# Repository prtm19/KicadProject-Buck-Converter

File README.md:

Hello, this is my project, Buck Converter. We convert 12V DC to 5V DC using a voltage Regulator. In our project, we use LM2496 Voltage regulator IC.

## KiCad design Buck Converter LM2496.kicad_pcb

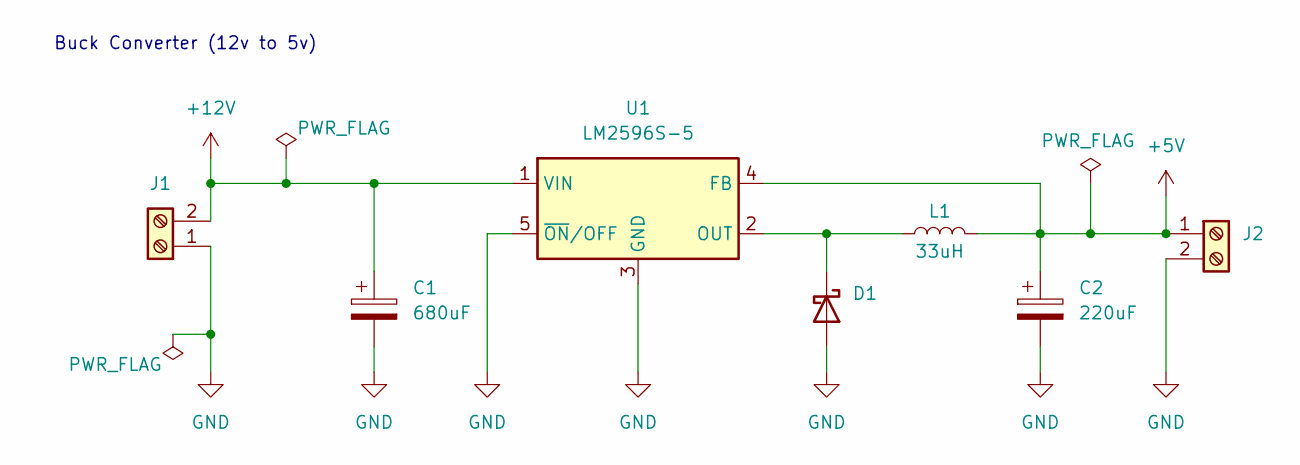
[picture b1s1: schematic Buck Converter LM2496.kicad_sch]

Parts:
C1: 680uF; CP_Radial_D8.0mm_P5.00mm
C2: 220uF; CP_Radial_D6.3mm_P2.50mm
D1: D_Schottky; D_SMA
J1, J2: Screw_Terminal_01x02; TerminalBlock_Phoenix_MKDS-1,5-2-5.08_1x02_P5.08mm_Horizont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
L1: 33uH; L_APV_APH0840
U1: LM2596S-5; TO-263-5_TabPin3

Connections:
+5V: C2.1, J2.1, L1.2, U1.4 (FB)
+12V: C1.1, J1.2, U1.1 (VIN)
GND: C1.2, C2.2, D1.2 (A), J1.1, J2.2, U1.3 (GND), U1.5 (~ON/OFF)
unnamed: D1.1 (K), L1.1, U1.2 (OUT)

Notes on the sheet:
Buck Converter (12v to 5v)

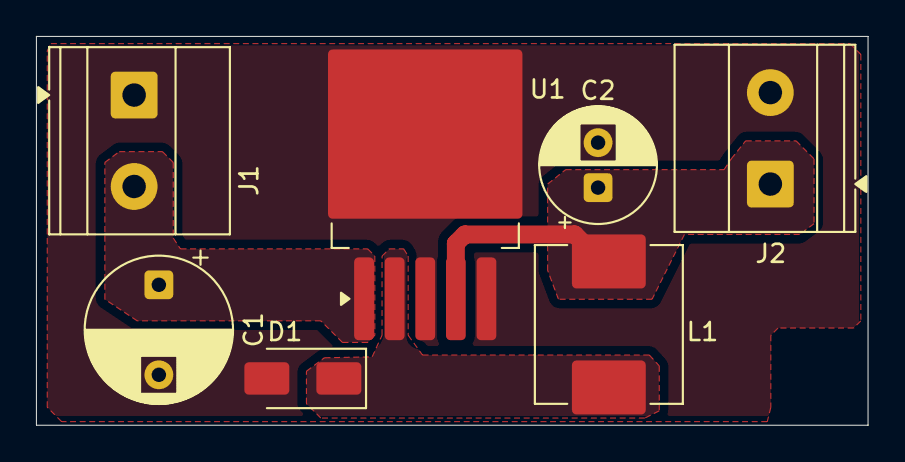
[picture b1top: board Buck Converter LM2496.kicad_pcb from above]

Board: 2 copper layers, 46.2 x 21.6 mm, 7 parts (0 on the bottom side), 4 nets.

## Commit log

2025-11-17 Initial file
2025-11-17 Add Readme file
